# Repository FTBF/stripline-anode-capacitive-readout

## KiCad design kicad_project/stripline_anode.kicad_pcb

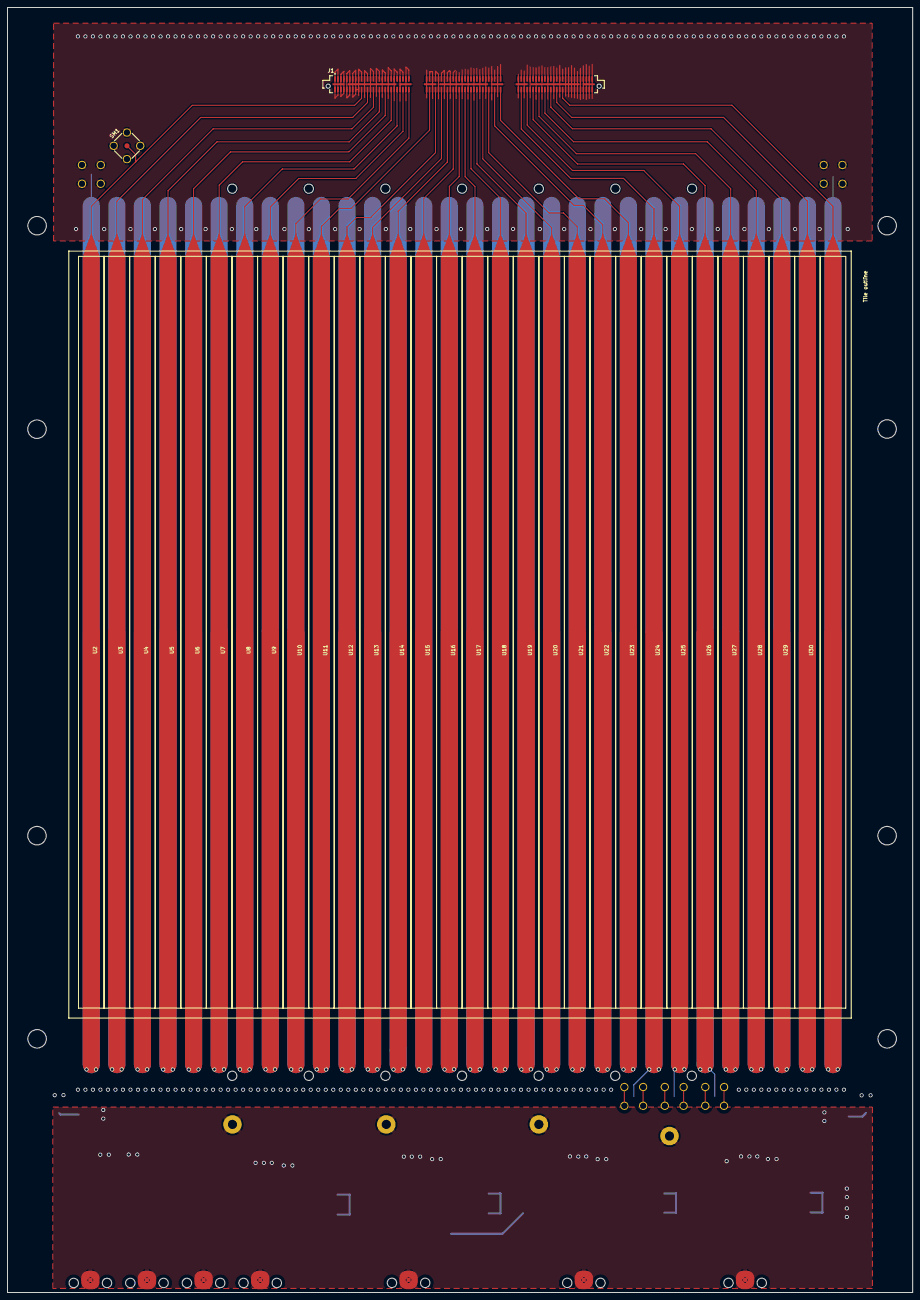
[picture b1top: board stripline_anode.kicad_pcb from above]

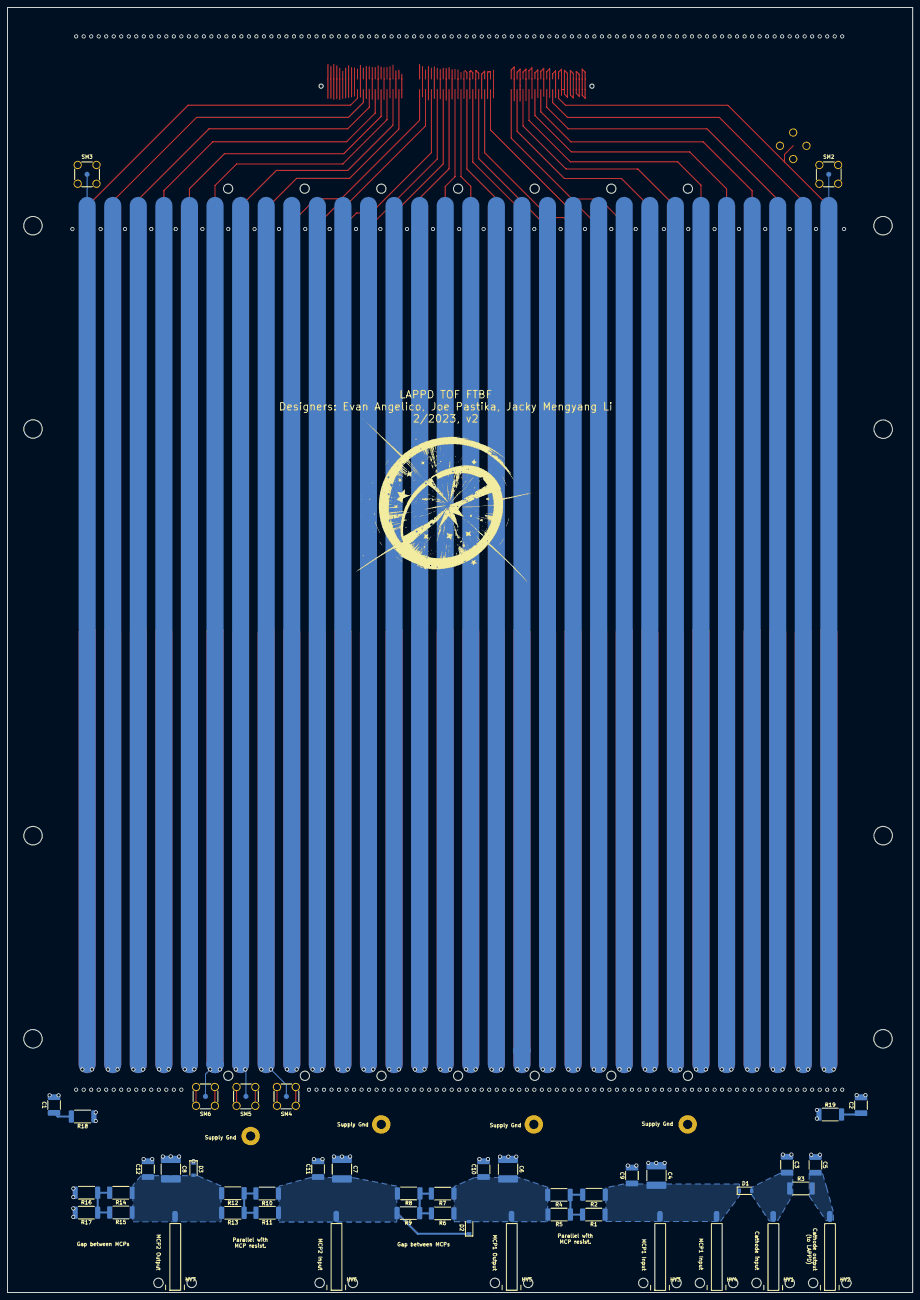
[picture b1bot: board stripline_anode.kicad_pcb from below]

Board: 6 copper layers, 244.9 x 347.7 mm, 82 parts (50 on the bottom side), 44 nets.

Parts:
C1, C2: 0.1 uF; C_1812_4532Metric_Pad1.57x3.40mm_HandSolder
C3, C5, C9, C10, C11, C12: 100 pF; C_1812_4532Metric_Pad1.57x3.40mm_HandSolder
C4, C6, C7, C8: 10 nF; C_2220_5650Metric_Pad1.97x5.40mm_HandSolder
D1, D2, D3: Zener 200V; D_SOD-123
HV1, HV2, HV3, HV4, HV5, HV6, HV7: Conn_01x02; SHV_cable_interface
J1: QRM8-078-05.0-L-D-A; SAMTEC_QRM8-078-05.0-L-D-A
POGO1, POGO2, POGO3, POGO4: Conn_01x01; MountingHole_2.5mm_Pad
R1, R2, R4, R5, R6, R7, R8, R9, R10, R11, R12, R13, R14, R15, R16, R17: R; R_2512_6332Metric_Pad1.40x3.35mm_HandSolder
R3: 100k; R_2512_6332Metric_Pad1.40x3.35mm_HandSolder
R18, R19: 200; R_2512_6332Metric_Pad1.40x3.35mm_HandSolder
SM1, SM2, SM3, SM4, SM5, SM6: Conn_Coaxial; SMA_Johnson_142-0711-271
U1, U2, U3, U4, U5, U6, U7, U8, U9, U10, U11, U12, U13, U14, U15, U16, U17, U18, U19, U20, U21, U22, U23, U24, U25, U26, U27, U28, U29, U30: anode_pad; stripline_30

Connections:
/GND: C1.2, C2.2, J1.01, J1.02, J1.03, J1.04, J1.05, J1.06, J1.07, J1.08, J1.09, J1.10, J1.11, J1.12, J1.13, J1.14, J1.15, J1.16, J1.17, J1.18, J1.19, J1.21, J1.22, J1.23, J1.25, J1.26, J1.27, J1.29, J1.30, J1.31, J1.33, J1.34, J1.35, J1.37, J1.38, J1.39, J1.41, J1.42, J1.43, J1.45, J1.46, J1.47, J1.49, J1.50, J1.51, J1.53, J1.54, J1.55, J1.57, J1.58, J1.59, J1.61, J1.62, J1.63, J1.65, J1.66, J1.67, J1.69, J1.70, J1.71, J1.73, J1.74, J1.75, J1.77, J1.78, J1.79, J1.81, J1.82, J1.83, J1.85, J1.86, J1.87, J1.89, J1.90, J1.91, J1.93, J1.94, J1.95, J1.97, J1.98, J1.99, J1.101, J1.102, J1.103, J1.105, J1.106, J1.107, J1.109, J1.110, J1.111, J1.113, J1.114, J1.115, J1.117, J1.118, J1.119, J1.121, J1.122, J1.123, J1.125, J1.126, J1.127, J1.129, J1.130, J1.131, J1.133, J1.134, J1.135, J1.137, J1.138, J1.139, J1.140, J1.141, J1.142, J1.143, J1.144, J1.145, J1.146, J1.147, J1.148, J1.149, J1.150, J1.151, J1.152, J1.153, J1.154, J1.155, J1.156, J1.G1, J1.G2, J1.G3, J1.G4, J1.G5, J1.G6, J1.G7, J1.G8, J1.G9, SM1.2 (Ext), SM2.2 (Ext), SM3.2 (Ext), SM4.2 (Ext), SM5.2 (Ext), SM6.2 (Ext)
/High voltage distribution/cath-in: C3.2, D1.2 (A), HV1.1, R3.1
/High voltage distribution/cath_out: C5.2, HV2.1, R3.2
/High voltage distribution/mcp1input: C4.2, C9.1, D1.1 (K), HV3.1, HV4.1, R1.1, R2.1
/High voltage distribution/mcp1output: C6.2, C10.1, D2.2 (A), HV5.1, R4.2, R5.2, R6.1, R7.1
/High voltage distribution/mcp2input: C7.2, C11.1, D2.1 (K), HV6.1, R8.2, R9.2, R10.1, R11.1
/High voltage distribution/mcp2output: C8.2, C12.1, D3.2 (A), HV7.1, R12.2, R13.2, R14.1, R15.1
/High voltage distribution/supply-gnd: C3.1, C4.1, C5.1, C6.1, C7.1, C8.1, C9.2, C10.2, C11.2, C12.2, D3.1 (K), HV1.2, HV2.2, HV3.2, HV4.2, HV5.2, HV6.2, HV7.2, POGO1.1, POGO2.1, POGO3.1, POGO4.1, R16.2, R17.2, R18.1, R19.1
/a1: J1.20, SM1.1 (In), SM2.1 (In), U1.1
/a2: J1.24, U2.1
/a3: J1.28, U3.1
/a4: J1.32, U4.1
/a5: J1.36, U5.1
/a6: J1.40, U6.1
/a7: J1.44, U7.1
/a8: J1.48, U8.1
/a9: J1.52, U9.1
/a10: J1.56, U10.1
/b1: J1.60, U11.1
/b2: J1.64, U12.1
/b3: J1.68, U13.1
/b4: J1.72, U14.1
/b5: J1.76, U15.1
/b6: J1.80, U16.1
/b7: J1.84, U17.1
/b8: J1.88, U18.1
/b9: J1.92, U19.1
/b10: J1.96, U20.1
/c1: J1.100, U21.1
/c2: J1.104, U22.1
/c3: J1.108, SM4.1 (In), U23.1
/c4: J1.112, SM5.1 (In), U24.1
/c5: J1.116, SM6.1 (In), U25.1
/c6: J1.120, U26.1
/c7: J1.124, U27.1
/c8: J1.128, U28.1
/c9: J1.132, U29.1
/c10: J1.136, SM3.1 (In), U30.1
unnamed: C1.1, R18.2
unnamed: C2.1, R19.2
unnamed: R1.2, R2.2, R4.1, R5.1
unnamed: R6.2, R7.2, R8.1, R9.1
unnamed: R10.2, R11.2, R12.1, R13.1
unnamed: R14.2, R15.2, R16.1, R17.1

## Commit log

2022-10-19 This represents minimal changes from the 'V2' of stripline capacitively coupled readout by Jacky uploaded to the psec library as item 373. Starting point for this repo, which will be dedicated to mak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
2022-11-10 managed footprints into a proper pretty library
2022-11-10 Changed footprints to match new local footprint library. Redid edge cuts and user-drawings layer to have a well-positioning of ultem frame mounting holes. Put in four of those mounting holes, a few m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
2022-11-11 Various updates - Added pogo pin mounting board holes - Added additional Ultem frame mounting holes - Added "funnels" to ends of pickup striplines - Reduced size of loop around traces on back side of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
2022-11-11 Add updated readme
2022-12-06 Schematic added for HV circuit draft 1
2022-12-06 replaced narrow back traces with wide traces and corrected mechamical hole diameters
2022-12-12 Schematic done for HV-circuit. Would like to merge before making layout changes, as some layout changes have been made on other branch and I'm not sure how it will be handled in git
2022-12-14 First draft layout of HV circuit. Things to refine: (1) ground return pads / mounting holes for gnd return. (2) Idea of how the high voltage inputs/outputs actually hook up to the LAPPD and incoming 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
2023-01-27 A close to final version of high voltage circuitry, after having decided to go with SHV cable ends soldered on to SMD pads, potted, and strain relieved by zip ties. Also added SMA ports. This is one 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
2023-02-03 Made adjustments to all via aspect ratios to fit basic standards of PCB way and a 5mm board. Moved some of the copper pours on the HV circuit side. About to dive into adjusting gnd stitching and gnd 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
2023-02-10 Board design is ready for production.
2023-02-10 Added gerbers and schem
2023-02-16 Change to the SHV cable layout to make slightly larger for shield soldering.
2023-02-17 Added logo silkscreen and footprint.
2023-03-31 As purchased in Mar 2023
